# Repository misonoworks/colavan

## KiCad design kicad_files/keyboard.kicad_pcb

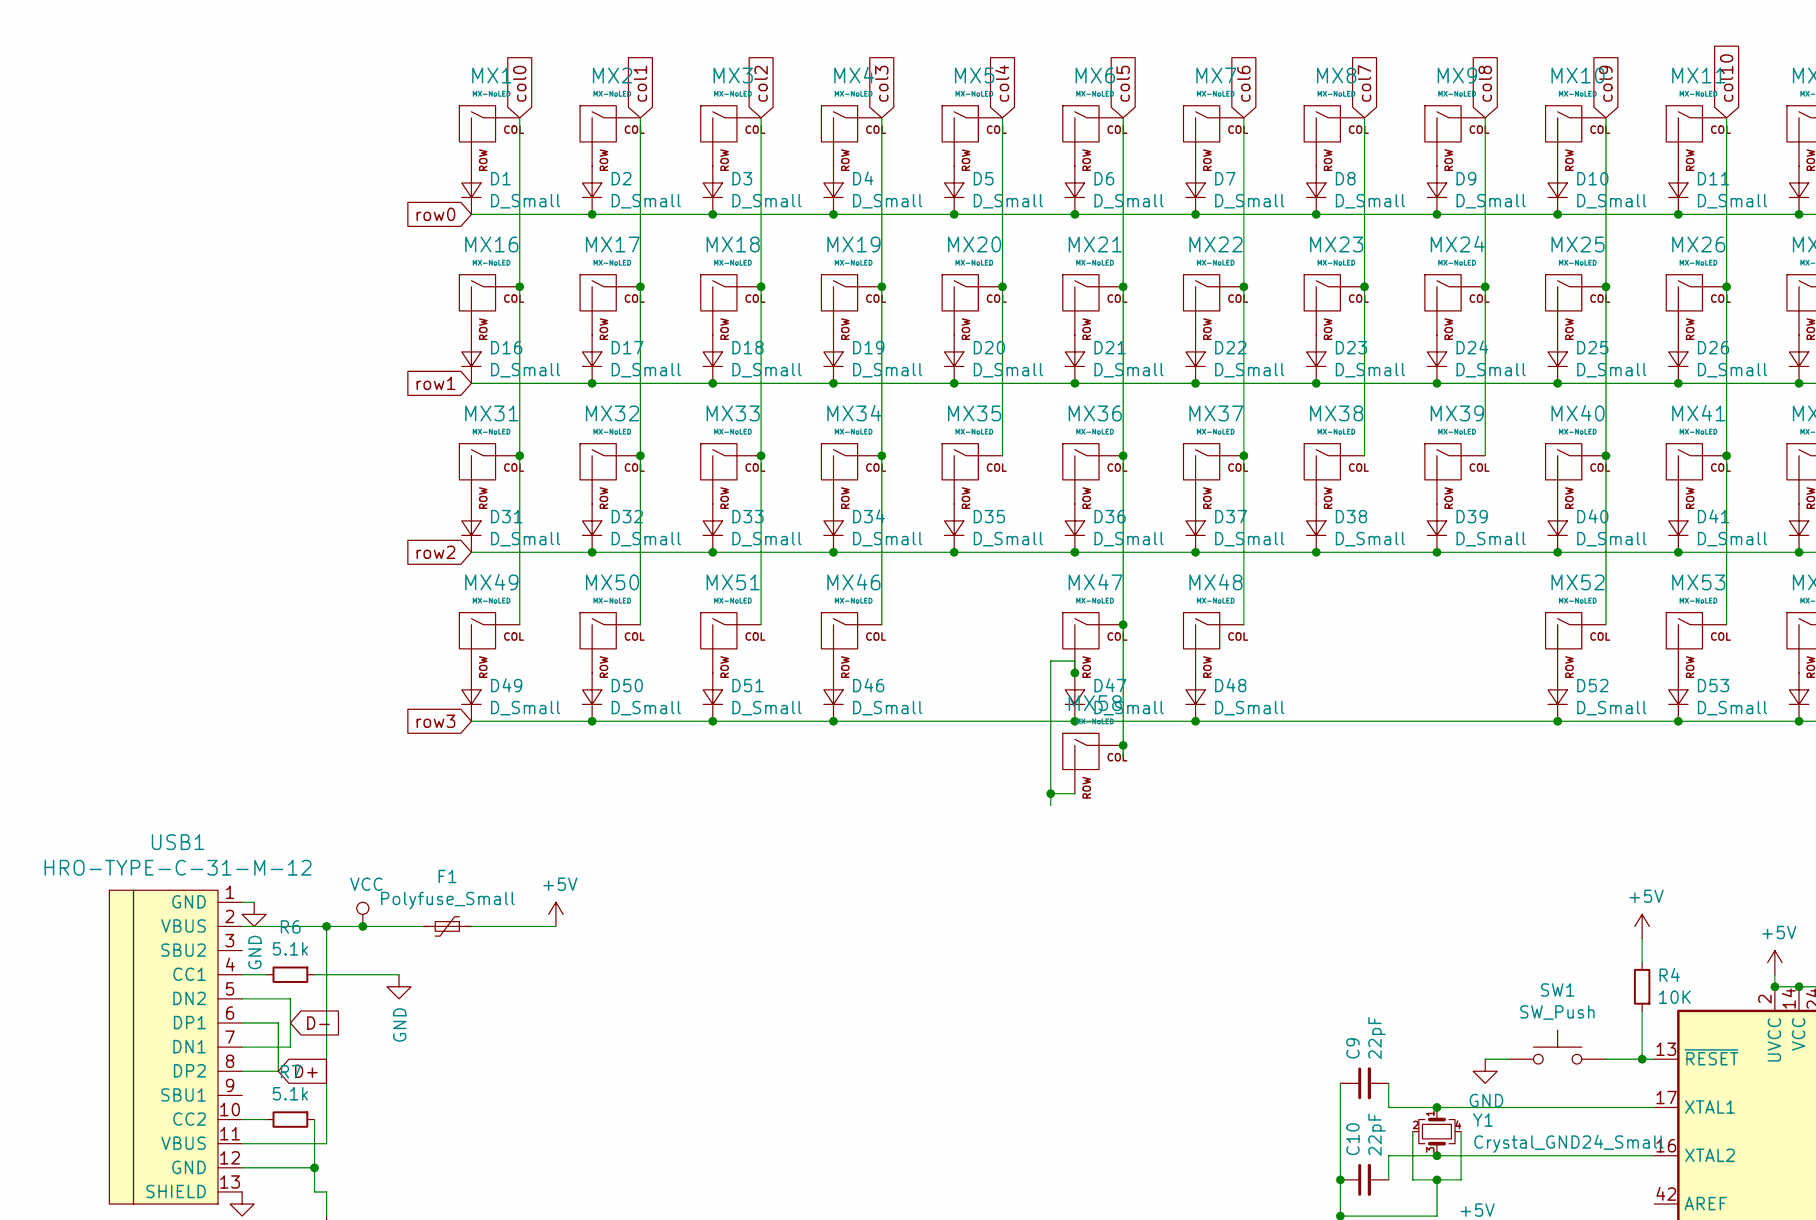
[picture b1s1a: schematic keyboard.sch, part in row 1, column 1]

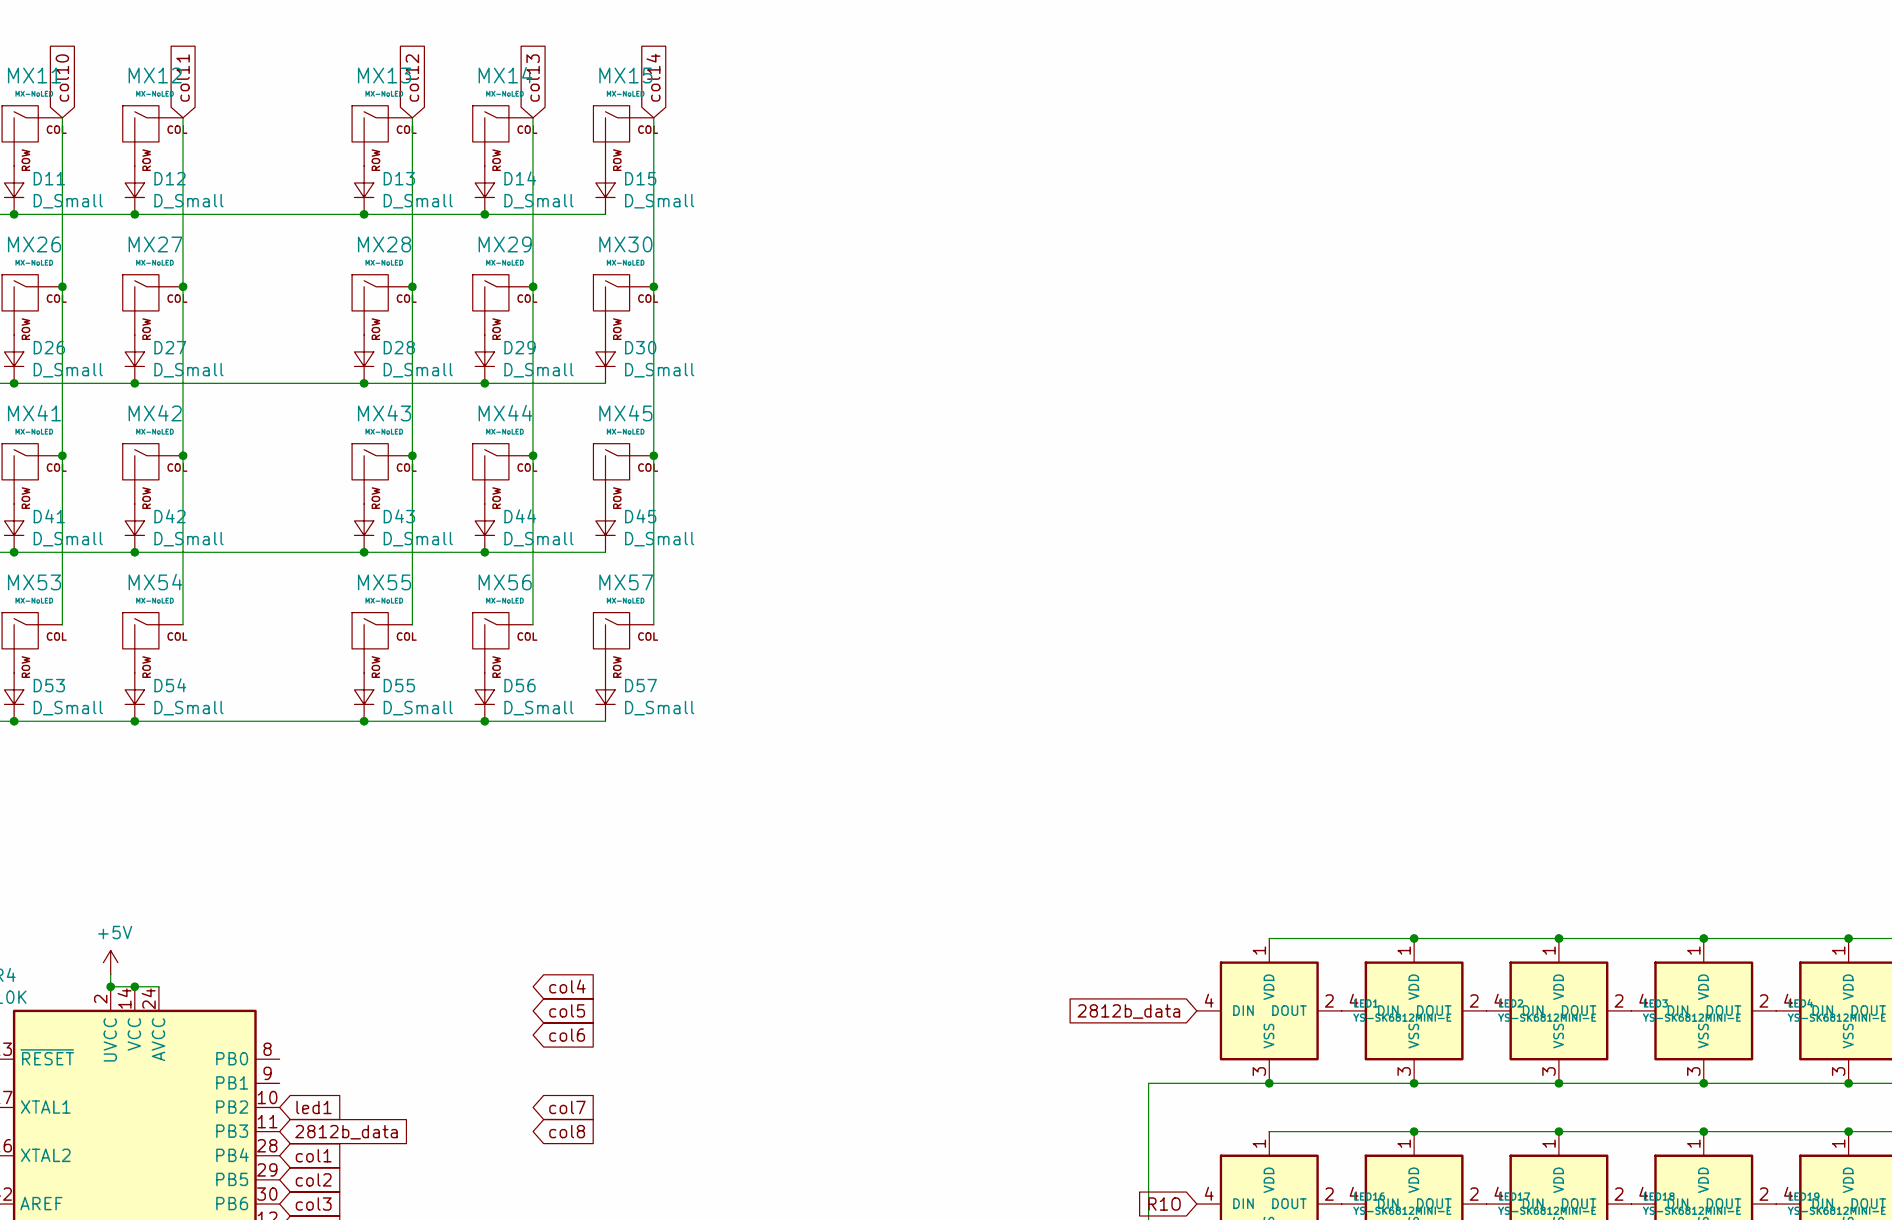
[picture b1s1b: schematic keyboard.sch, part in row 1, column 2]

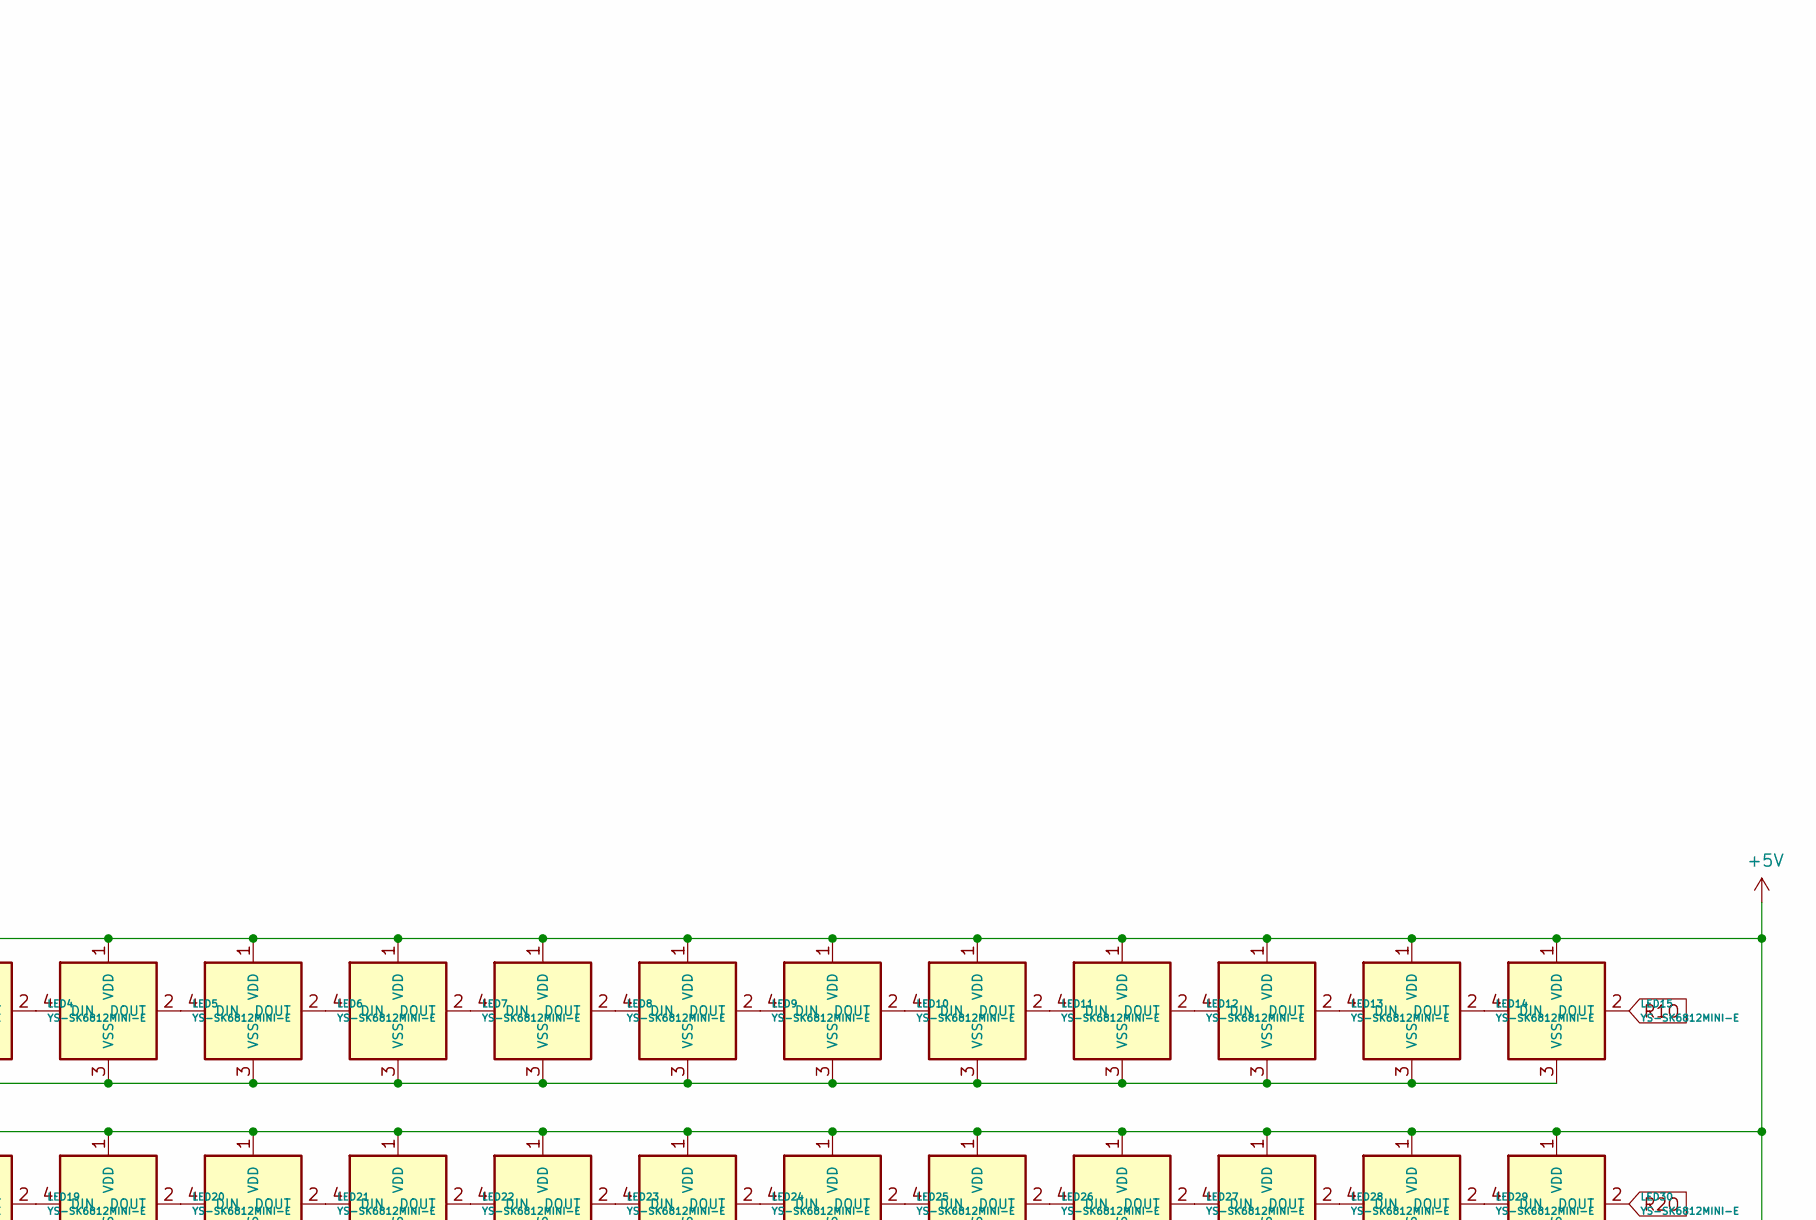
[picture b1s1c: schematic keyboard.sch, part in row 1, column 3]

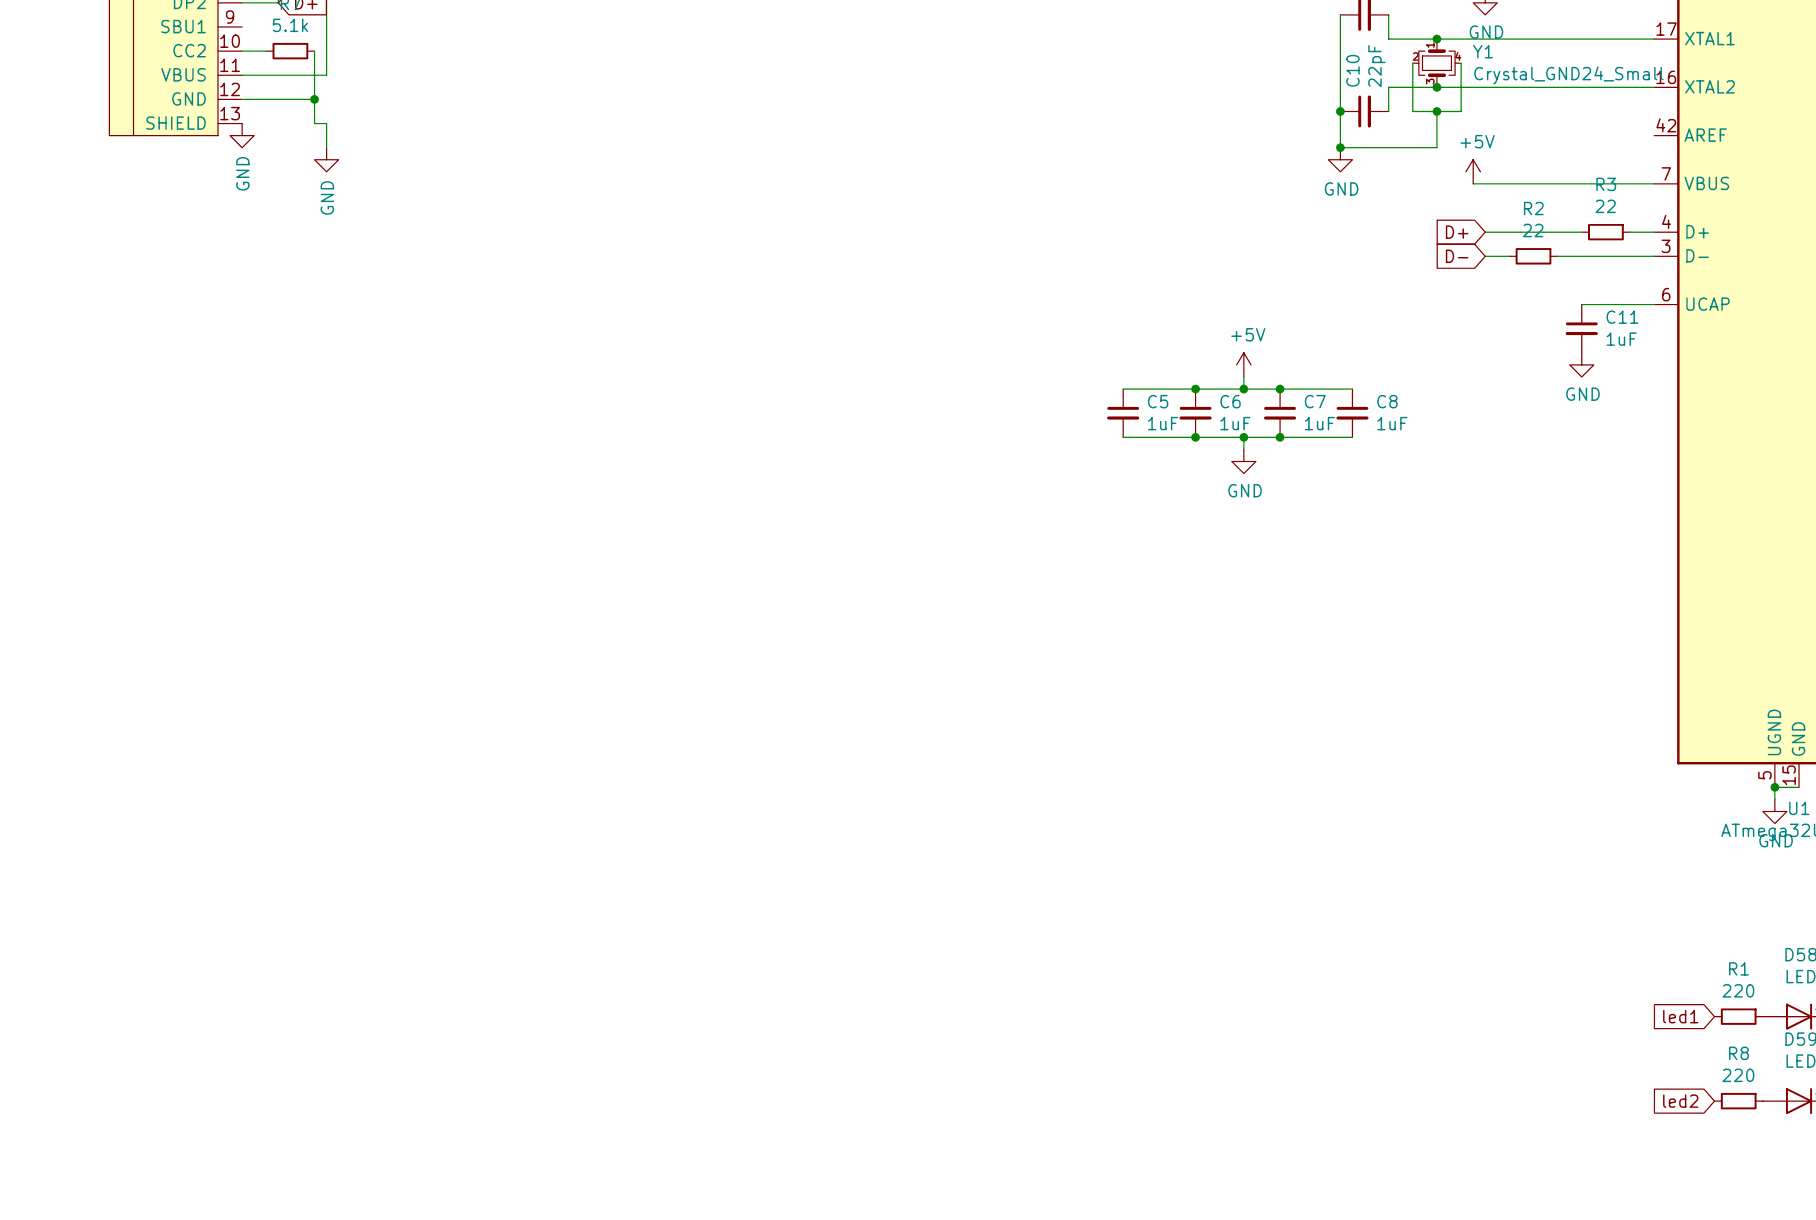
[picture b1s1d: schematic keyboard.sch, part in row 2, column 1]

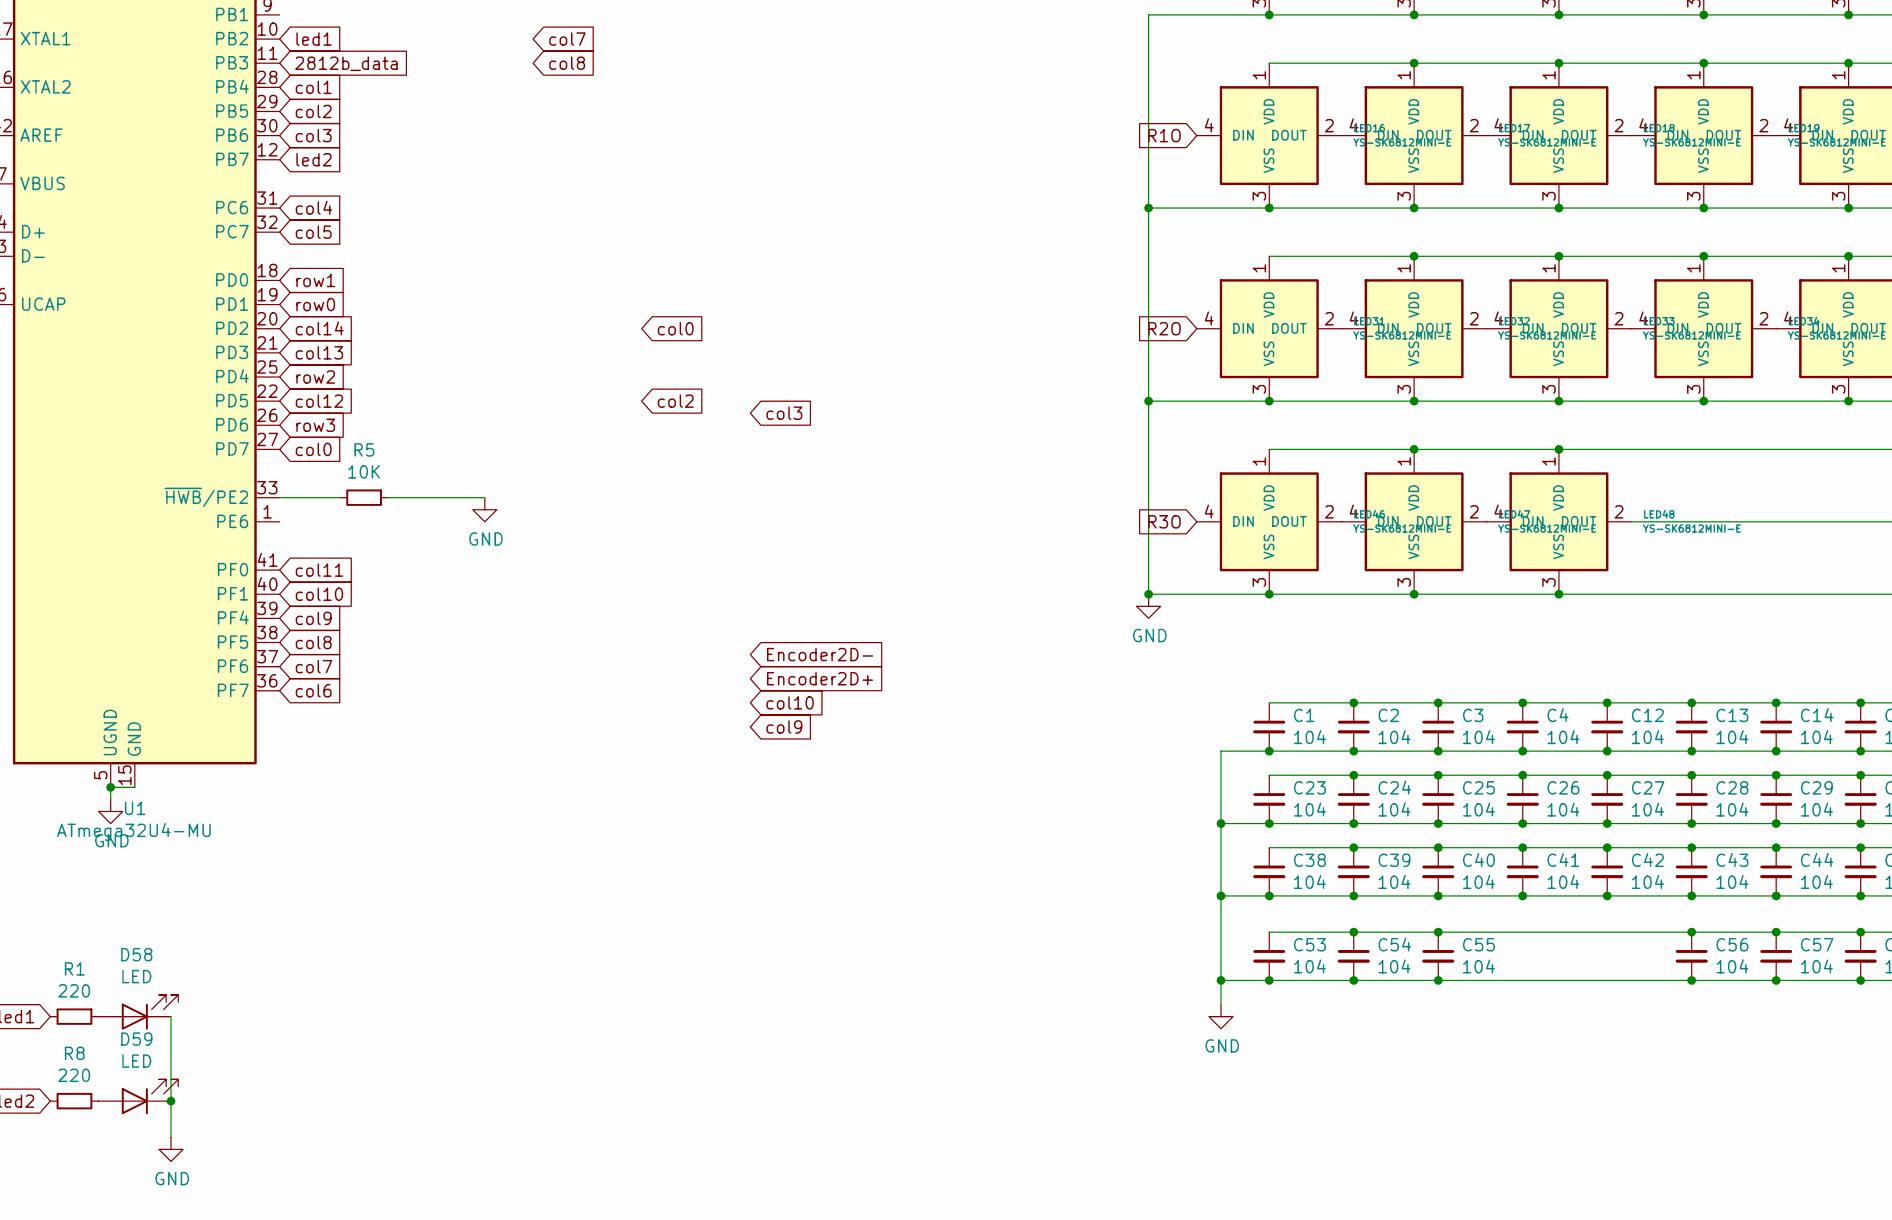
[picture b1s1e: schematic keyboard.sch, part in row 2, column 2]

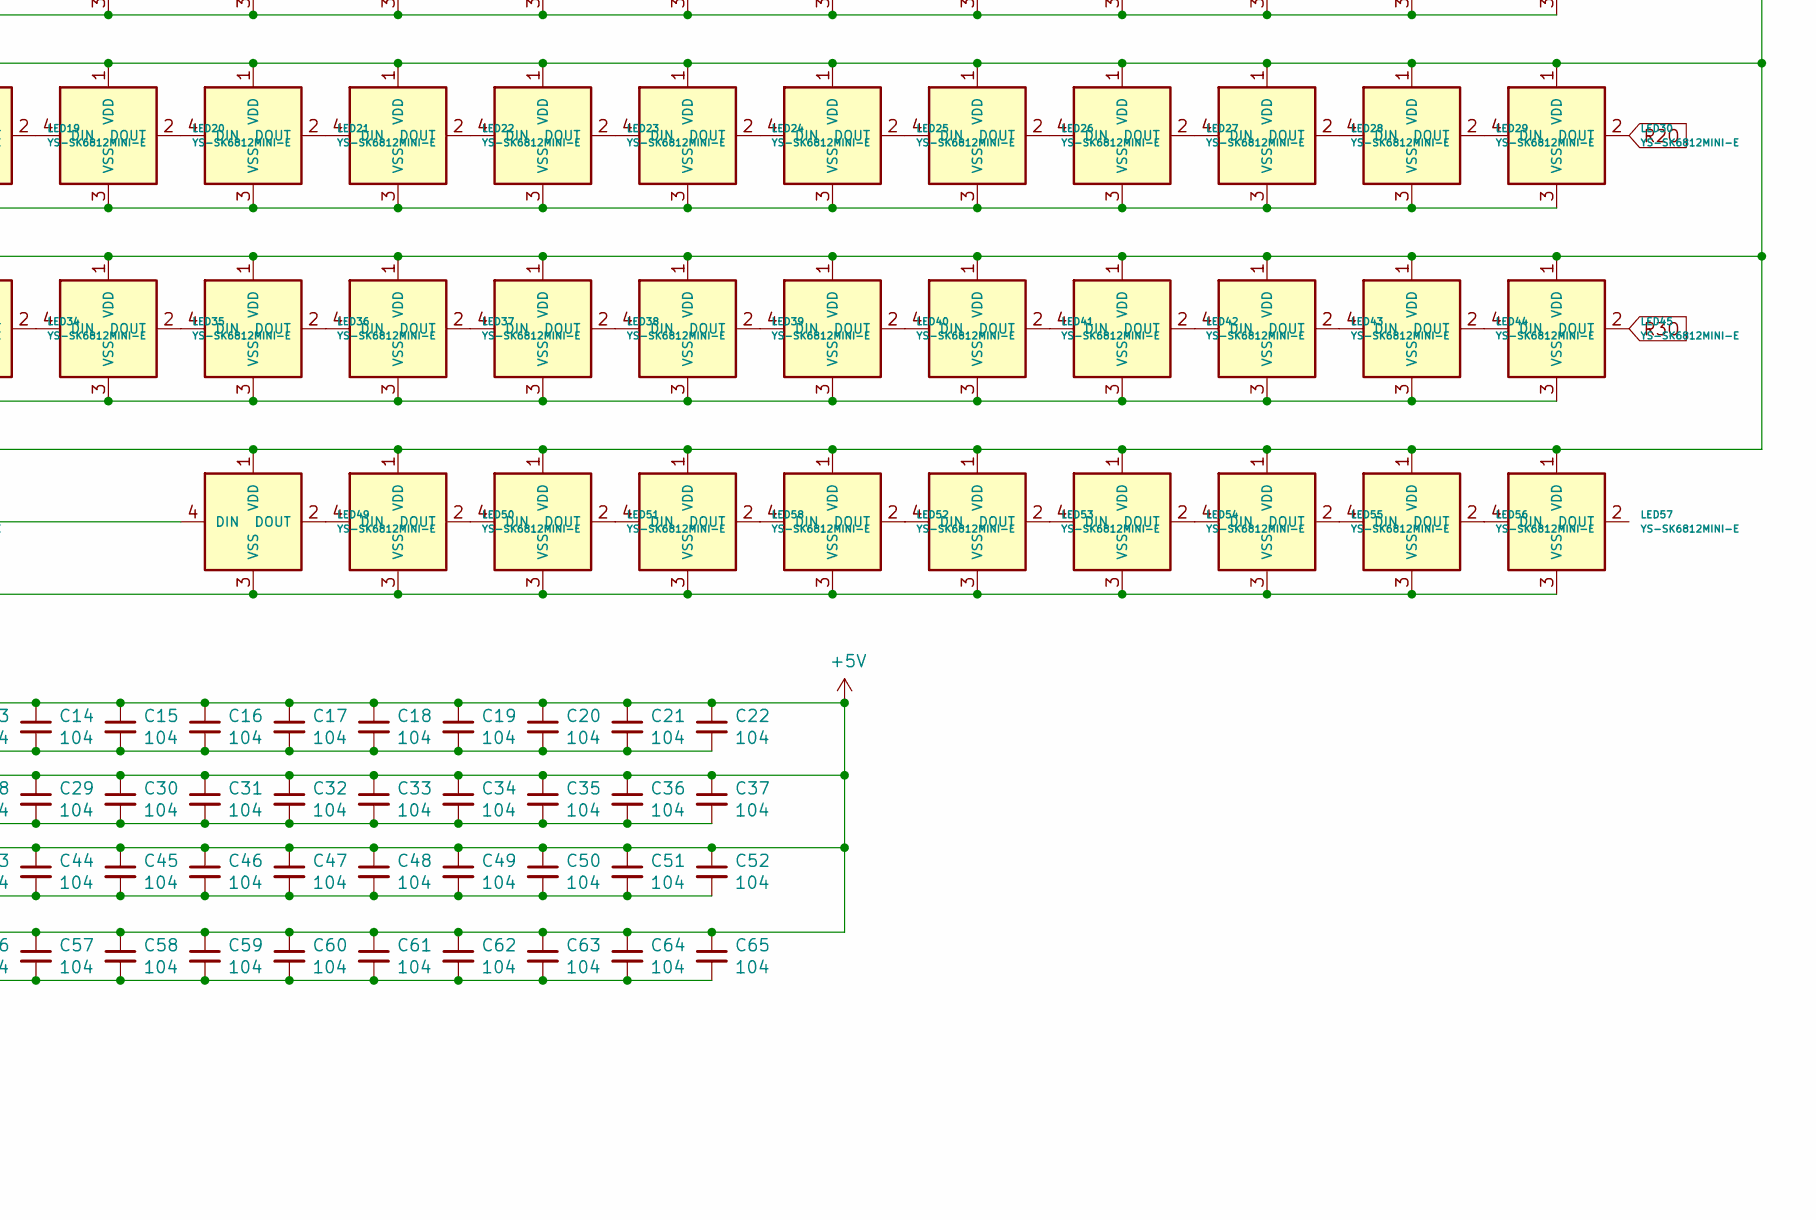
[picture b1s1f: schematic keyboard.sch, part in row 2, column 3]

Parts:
C1, C2, C3, C4, C12, C13, C14, C15, C16, C17, C18, C19, C20, C21, C22, C23, C24, C25, C26, C27, C28, C29, C30, C31, C32, C33, C34, C35, C36, C37, C38, C39, C40, C41, C42, C43, C44, C45, C46, C47, C48, C49, C50, C51, C52, C53, C54, C55, C56, C57, C58, C59, C60, C61, C62, C63, C64, C65: 104; C_0402_1005Metric
C5, C6, C7, C8, C11: 1uF; C_0402_1005Metric
C9, C10: 22pF; C_0402_1005Metric
D1, D2, D3, D4, D5, D6, D7, D8, D9, D10, D11, D12, D13, D14, D15, D16, D17, D18, D19, D20, D21, D22, D23, D24, D25, D26, D27, D28, D29, D30, D31, D32, D33, D34, D35, D36, D37, D38, D39, D40, D41, D42, D43, D44, D45, D46, D47, D48, D49, D50, D51, D52, D53, D54, D55, D56, D57: D_Small; D_SOD-123
D58, D59: LED; LED_D3.0mm
F1: Polyfuse_Small; Fuse_1206_3216Metric
LED1, LED2, LED3, LED4, LED5, LED6, LED7, LED8, LED9, LED10, LED11, LED12, LED13, LED14, LED15, LED16, LED17, LED18, LED19, LED20, LED21, LED22, LED23, LED24, LED25, LED26, LED27, LED28, LED29, LED30, LED31, LED32, LED33, LED34, LED35, LED36, LED37, LED38, LED39, LED40, LED41, LED42, LED43, LED44, LED45, LED46, LED47, LED48, LED49, LED50, LED51, LED52, LED53, LED54, LED55, LED56, LED57, LED58: YS-SK6812MINI-E
MX1, MX2, MX3, MX4, MX5, MX6, MX7, MX8, MX9, MX10, MX11, MX13, MX14, MX15, MX17, MX18, MX19, MX20, MX21, MX22, MX23, MX24, MX25, MX26, MX28, MX29, MX30, MX32, MX33, MX34, MX35, MX36, MX37, MX38, MX39, MX40, MX41, MX42, MX43, MX44, MX45, MX50, MX51, MX52, MX53, MX55, MX56, MX57: MX-NoLED; MX-1U-NoLED
MX12, MX31: MX-NoLED; MX-1.75U-NoLED
MX16, MX49, MX54, MX58: MX-NoLED; MX-1.25U-NoLED
MX27: MX-NoLED; MX-1.5U-NoLED
MX46: MX-NoLED; MX-2.25U-ReversedStabilizers-NoLED
MX47: MX-NoLED; MX-6.25U-ReversedStabilizers-NoLED
MX48: MX-NoLED; MX-2.75U-ReversedStabilizers-NoLED
R1, R8: 220; R_0402_1005Metric
R2, R3: 22; R_0603_1608Metric
R4, R5: 10K; R_0603_1608Metric
R6, R7: 5.1k; R_0603_1608Metric
SW1: SW_Push; SKQG-1155865
U1: ATmega32U4-MU; QFN-44-1EP_7x7mm_P0.5mm_EP5.2x5.2mm
USB1: HRO-TYPE-C-31-M-12; HRO-TYPE-C-31-M-12-HandSoldering
Y1: Crystal_GND24_Small; Crystal_SMD_3225-4Pin_3.2x2.5mm

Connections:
2812b_data: LED1.4 (DIN), U1.11 (PB3)
+5V: C1.1, C2.1, C3.1, C4.1, C5.1, C6.1, C7.1, C8.1, C12.1, C13.1, C14.1, C15.1, C16.1, C17.1, C18.1, C19.1, C20.1, C21.1, C22.1, C23.1, C24.1, C25.1, C26.1, C27.1, C28.1, C29.1, C30.1, C31.1, C32.1, C33.1, C34.1, C35.1, C36.1, C37.1, C38.1, C39.1, C40.1, C41.1, C42.1, C43.1, C44.1, C45.1, C46.1, C47.1, C48.1, C49.1, C50.1, C51.1, C52.1, C53.1, C54.1, C55.1, C56.1, C57.1, C58.1, C59.1, C60.1, C61.1, C62.1, C63.1, C64.1, C65.1, F1.1, LED1.1 (VDD), LED2.1 (VDD), LED3.1 (VDD), LED4.1 (VDD), LED5.1 (VDD), LED6.1 (VDD), LED7.1 (VDD), LED8.1 (VDD), LED9.1 (VDD), LED10.1 (VDD), LED11.1 (VDD), LED12.1 (VDD), LED13.1 (VDD), LED14.1 (VDD), LED15.1 (VDD), LED16.1 (VDD), LED17.1 (VDD), LED18.1 (VDD), LED19.1 (VDD), LED20.1 (VDD), LED21.1 (VDD), LED22.1 (VDD), LED23.1 (VDD), LED24.1 (VDD), LED25.1 (VDD), LED26.1 (VDD), LED27.1 (VDD), LED28.1 (VDD), LED29.1 (VDD), LED30.1 (VDD), LED31.1 (VDD), LED32.1 (VDD), LED33.1 (VDD), LED34.1 (VDD), LED35.1 (VDD), LED36.1 (VDD), LED37.1 (VDD), LED38.1 (VDD), LED39.1 (VDD), LED40.1 (VDD), LED41.1 (VDD), LED42.1 (VDD), LED43.1 (VDD), LED44.1 (VDD), LED45.1 (VDD), LED46.1 (VDD), LED47.1 (VDD), LED48.1 (VDD), LED49.1 (VDD), LED50.1 (VDD), LED51.1 (VDD), LED52.1 (VDD), LED53.1 (VDD), LED54.1 (VDD), LED55.1 (VDD), LED56.1 (VDD), LED57.1 (VDD), LED58.1 (VDD), R4.2, U1.2 (UVCC), U1.7 (VBUS), U1.14 (VCC), U1.24 (AVCC), U1.34 (VCC), U1.44 (AVCC)
D+: R3.2, USB1.6 (DP1), USB1.8 (DP2)
D-: R2.2, USB1.5 (DN2), USB1.7 (DN1)
GND: C1.2, C2.2, C3.2, C4.2, C5.2, C6.2, C7.2, C8.2, C9.1, C10.1, C11.2, C12.2, C13.2, C14.2, C15.2, C16.2, C17.2, C18.2, C19.2, C20.2, C21.2, C22.2, C23.2, C24.2, C25.2, C26.2, C27.2, C28.2, C29.2, C30.2, C31.2, C32.2, C33.2, C34.2, C35.2, C36.2, C37.2, C38.2, C39.2, C40.2, C41.2, C42.2, C43.2, C44.2, C45.2, C46.2, C47.2, C48.2, C49.2, C50.2, C51.2, C52.2, C53.2, C54.2, C55.2, C56.2, C57.2, C58.2, C59.2, C60.2, C61.2, C62.2, C63.2, C64.2, C65.2, D58.1 (K), D59.1 (K), LED1.3 (VSS), LED2.3 (VSS), LED3.3 (VSS), LED4.3 (VSS), LED5.3 (VSS), LED6.3 (VSS), LED7.3 (VSS), LED8.3 (VSS), LED9.3 (VSS), LED10.3 (VSS), LED11.3 (VSS), LED12.3 (VSS), LED13.3 (VSS), LED14.3 (VSS), LED15.3 (VSS), LED16.3 (VSS), LED17.3 (VSS), LED18.3 (VSS), LED19.3 (VSS), LED20.3 (VSS), LED21.3 (VSS), LED22.3 (VSS), LED23.3 (VSS), LED24.3 (VSS), LED25.3 (VSS), LED26.3 (VSS), LED27.3 (VSS), LED28.3 (VSS), LED29.3 (VSS), LED30.3 (VSS), LED31.3 (VSS), LED32.3 (VSS), LED33.3 (VSS), LED34.3 (VSS), LED35.3 (VSS), LED36.3 (VSS), LED37.3 (VSS), LED38.3 (VSS), LED39.3 (VSS), LED40.3 (VSS), LED41.3 (VSS), LED42.3 (VSS), LED43.3 (VSS), LED44.3 (VSS), LED45.3 (VSS), LED46.3 (VSS), LED47.3 (VSS), LED48.3 (VSS), LED49.3 (VSS), LED50.3 (VSS), LED51.3 (VSS), LED52.3 (VSS), LED53.3 (VSS), LED54.3 (VSS), LED55.3 (VSS), LED56.3 (VSS), LED57.3 (VSS), LED58.3 (VSS), R5.1, R6.1, R7.1, SW1.1, U1.5 (UGND), U1.15 (GND), U1.23 (GND), U1.35 (GND), U1.43 (GND), U1.45 (GND), USB1.1 (GND), USB1.12 (GND), USB1.13 (SHIELD), Y1.2, Y1.4
unnamed: C9.2, U1.17 (XTAL1), Y1.1
unnamed: C10.2, U1.16 (XTAL2), Y1.3
unnamed: C11.1, U1.6 (UCAP)
unnamed: D1.2 (A), MX1.2 (ROW)
unnamed: D2.2 (A), MX2.2 (ROW)
unnamed: D3.2 (A), MX3.2 (ROW)
unnamed: D4.2 (A), MX4.2 (ROW)
unnamed: D5.2 (A), MX5.2 (ROW)
unnamed: D6.2 (A), MX6.2 (ROW)
unnamed: D7.2 (A), MX7.2 (ROW)
unnamed: D8.2 (A), MX8.2 (ROW)
unnamed: D9.2 (A), MX9.2 (ROW)
unnamed: D10.2 (A), MX10.2 (ROW)
unnamed: D11.2 (A), MX11.2 (ROW)
unnamed: D12.2 (A), MX12.2 (ROW)
unnamed: D13.2 (A), MX13.2 (ROW)
unnamed: D14.2 (A), MX14.2 (ROW)
unnamed: D15.2 (A), MX15.2 (ROW)
unnamed: D16.2 (A), MX16.2 (ROW)
unnamed: D17.2 (A), MX17.2 (ROW)
unnamed: D18.2 (A), MX18.2 (ROW)
unnamed: D19.2 (A), MX19.2 (ROW)
unnamed: D20.2 (A), MX20.2 (ROW)
unnamed: D21.2 (A), MX21.2 (ROW)
unnamed: D22.2 (A), MX22.2 (ROW)
unnamed: D23.2 (A), MX23.2 (ROW)
unnamed: D24.2 (A), MX24.2 (ROW)
unnamed: D25.2 (A), MX25.2 (ROW)
unnamed: D26.2 (A), MX26.2 (ROW)
unnamed: D27.2 (A), MX27.2 (ROW)
unnamed: D28.2 (A), MX28.2 (ROW)
unnamed: D29.2 (A), MX29.2 (ROW)
unnamed: D30.2 (A), MX30.2 (ROW)
unnamed: D31.2 (A), MX31.2 (ROW)
unnamed: D32.2 (A), MX32.2 (ROW)
unnamed: D33.2 (A), MX33.2 (ROW)
unnamed: D34.2 (A), MX34.2 (ROW)
unnamed: D35.2 (A), MX35.2 (ROW)
unnamed: D36.2 (A), MX36.2 (ROW)
unnamed: D37.2 (A), MX37.2 (ROW)
unnamed: D38.2 (A), MX38.2 (ROW)
unnamed: D39.2 (A), MX39.2 (ROW)
unnamed: D40.2 (A), MX40.2 (ROW)
unnamed: D41.2 (A), MX41.2 (ROW)
unnamed: D42.2 (A), MX42.2 (ROW)
unnamed: D43.2 (A), MX43.2 (ROW)
unnamed: D44.2 (A), MX44.2 (ROW)
unnamed: D45.2 (A), MX45.2 (ROW)
unnamed: D46.2 (A), MX46.2 (ROW)
unnamed: D47.2 (A), MX47.2 (ROW), MX58.2 (ROW)
unnamed: D48.2 (A), MX48.2 (ROW)
unnamed: D49.2 (A), MX49.2 (ROW)
unnamed: D50.2 (A), MX50.2 (ROW)
unnamed: D51.2 (A), MX51.2 (ROW)
unnamed: D52.2 (A), MX52.2 (ROW)
unnamed: D53.2 (A), MX53.2 (ROW)
unnamed: D54.2 (A), MX54.2 (ROW)
unnamed: D55.2 (A), MX55.2 (ROW)
unnamed: D56.2 (A), MX56.2 (ROW)
unnamed: D57.2 (A), MX57.2 (ROW)
unnamed: D58.2 (A), R1.1
unnamed: D59.2 (A), R8.1
unnamed: LED1.2 (DOUT), LED2.4 (DIN)
unnamed: LED2.2 (DOUT), LED3.4 (DIN)
unnamed: LED3.2 (DOUT), LED4.4 (DIN)
unnamed: LED4.2 (DOUT), LED5.4 (DIN)
unnamed: LED5.2 (DOUT), LED6.4 (DIN)
unnamed: LED6.2 (DOUT), LED7.4 (DIN)
unnamed: LED7.2 (DOUT), LED8.4 (DIN)
unnamed: LED8.2 (DOUT), LED9.4 (DIN)
unnamed: LED10.2 (DOUT), LED11.4 (DIN)
unnamed: LED9.2 (DOUT), LED10.4 (DIN)
unnamed: LED11.2 (DOUT), LED12.4 (DIN)
unnamed: LED12.2 (DOUT), LED13.4 (DIN)
unnamed: LED13.2 (DOUT), LED14.4 (DIN)
unnamed: LED14.2 (DOUT), LED15.4 (DIN)
unnamed: LED16.2 (DOUT), LED17.4 (DIN)
unnamed: LED17.2 (DOUT), LED18.4 (DIN)
unnamed: LED18.2 (DOUT), LED19.4 (DIN)
unnamed: LED19.2 (DOUT), LED20.4 (DIN)
unnamed: LED20.2 (DOUT), LED21.4 (DIN)
unnamed: LED21.2 (DOUT), LED22.4 (DIN)
unnamed: LED22.2 (DOUT), LED23.4 (DIN)
unnamed: LED23.2 (DOUT), LED24.4 (DIN)
unnamed: LED24.2 (DOUT), LED25.4 (DIN)
unnamed: LED25.2 (DOUT), LED26.4 (DIN)
unnamed: LED26.2 (DOUT), LED27.4 (DIN)
unnamed: LED27.2 (DOUT), LED28.4 (DIN)
unnamed: LED28.2 (DOUT), LED29.4 (DIN)
unnamed: LED29.2 (DOUT), LED30.4 (DIN)
unnamed: LED31.2 (DOUT), LED32.4 (DIN)
unnamed: LED32.2 (DOUT), LED33.4 (DIN)
unnamed: LED33.2 (DOUT), LED34.4 (DIN)
unnamed: LED34.2 (DOUT), LED35.4 (DIN)
unnamed: LED35.2 (DOUT), LED36.4 (DIN)
unnamed: LED36.2 (DOUT), LED37.4 (DIN)
unnamed: LED37.2 (DOUT), LED38.4 (DIN)
unnamed: LED38.2 (DOUT), LED39.4 (DIN)
unnamed: LED39.2 (DOUT), LED40.4 (DIN)
unnamed: LED40.2 (DOUT), LED41.4 (DIN)
unnamed: LED41.2 (DOUT), LED42.4 (DIN)
unnamed: LED42.2 (DOUT), LED43.4 (DIN)
unnamed: LED43.2 (DOUT), LED44.4 (DIN)
unnamed: LED44.2 (DOUT), LED45.4 (DIN)
unnamed: LED46.2 (DOUT), LED47.4 (DIN)
unnamed: LED47.2 (DOUT), LED48.4 (DIN)
unnamed: LED48.2 (DOUT), LED49.4 (DIN)
unnamed: LED49.2 (DOUT), LED50.4 (DIN)
unnamed: LED50.2 (DOUT), LED51.4 (DIN)
unnamed: LED51.2 (DOUT), LED58.4 (DIN)
unnamed: LED52.2 (DOUT), LED53.4 (DIN)
unnamed: LED52.4 (DIN), LED58.2 (DOUT)
unnamed: LED53.2 (DOUT), LED54.4 (DIN)
unnamed: LED54.2 (DOUT), LED55.4 (DIN)
unnamed: LED55.2 (DOUT), LED56.4 (DIN)
unnamed: LED56.2 (DOUT), LED57.4 (DIN)
unnamed: R2.1, U1.3 (D-)
unnamed: R3.1, U1.4 (D+)
unnamed: R4.1, SW1.2, U1.13 (~RESET)
unnamed: R5.2, U1.33 (~HWB~/PE2)
unnamed: R6.2, USB1.4 (CC1)
unnamed: R7.2, USB1.10 (CC2)
R1O: LED15.2 (DOUT), LED16.4 (DIN)
R2O: LED30.2 (DOUT), LED31.4 (DIN)
R3O: LED45.2 (DOUT), LED46.4 (DIN)
VCC: F1.2, USB1.2 (VBUS), USB1.11 (VBUS)
col0: MX1.1 (COL), MX16.1 (COL), MX31.1 (COL), MX49.1 (COL), U1.27 (PD7)
col1: MX2.1 (COL), MX17.1 (COL), MX32.1 (COL), MX50.1 (COL), U1.28 (PB4)
col2: MX3.1 (COL), MX18.1 (COL), MX33.1 (COL), MX51.1 (COL), U1.29 (PB5)
col3: MX4.1 (COL), MX19.1 (COL), MX34.1 (COL), MX46.1 (COL), U1.30 (PB6)
col4: MX5.1 (COL), MX20.1 (COL), MX35.1 (COL), U1.31 (PC6)
col5: MX6.1 (COL), MX21.1 (COL), MX36.1 (COL), MX47.1 (COL), MX58.1 (COL), U1.32 (PC7)
col6: MX7.1 (COL), MX22.1 (COL), MX37.1 (COL), MX48.1 (COL), U1.36 (PF7)
col7: MX8.1 (COL), MX23.1 (COL), MX38.1 (COL), U1.37 (PF6)
col8: MX9.1 (COL), MX24.1 (COL), MX39.1 (COL), U1.38 (PF5)
col9: MX10.1 (COL), MX25.1 (COL), MX40.1 (COL), MX52.1 (COL), U1.39 (PF4)
col10: MX11.1 (COL), MX26.1 (COL), MX41.1 (COL), MX53.1 (COL), U1.40 (PF1)
col11: MX12.1 (COL), MX27.1 (COL), MX42.1 (COL), MX54.1 (COL), U1.41 (PF0)
col12: MX13.1 (COL), MX28.1 (COL), MX43.1 (COL), MX55.1 (COL), U1.22 (PD5)
col13: MX14.1 (COL), MX29.1 (COL), MX44.1 (COL), MX56.1 (COL), U1.21 (PD3)
col14: MX15.1 (COL), MX30.1 (COL), MX45.1 (COL), MX57.1 (COL), U1.20 (PD2)
led1: R1.2, U1.10 (PB2)
led2: R8.2, U1.12 (PB7)
row0: D1.1 (K), D2.1 (K), D3.1 (K), D4.1 (K), D5.1 (K), D6.1 (K), D7.1 (K), D8.1 (K), D9.1 (K), D10.1 (K), D11.1 (K), D12.1 (K), D13.1 (K), D14.1 (K), D15.1 (K), U1.19 (PD1)
row1: D16.1 (K), D17.1 (K), D18.1 (K), D19.1 (K), D20.1 (K), D21.1 (K), D22.1 (K), D23.1 (K), D24.1 (K), D25.1 (K), D26.1 (K), D27.1 (K), D28.1 (K), D29.1 (K), D30.1 (K), U1.18 (PD0)
row2: D31.1 (K), D32.1 (K), D33.1 (K), D34.1 (K), D35.1 (K), D36.1 (K), D37.1 (K), D38.1 (K), D39.1 (K), D40.1 (K), D41.1 (K), D42.1 (K), D43.1 (K), D44.1 (K), D45.1 (K), U1.25 (PD4)
row3: D46.1 (K), D47.1 (K), D48.1 (K), D49.1 (K), D50.1 (K), D51.1 (K), D52.1 (K), D53.1 (K), D54.1 (K), D55.1 (K), D56.1 (K), D57.1 (K), U1.26 (PD6)

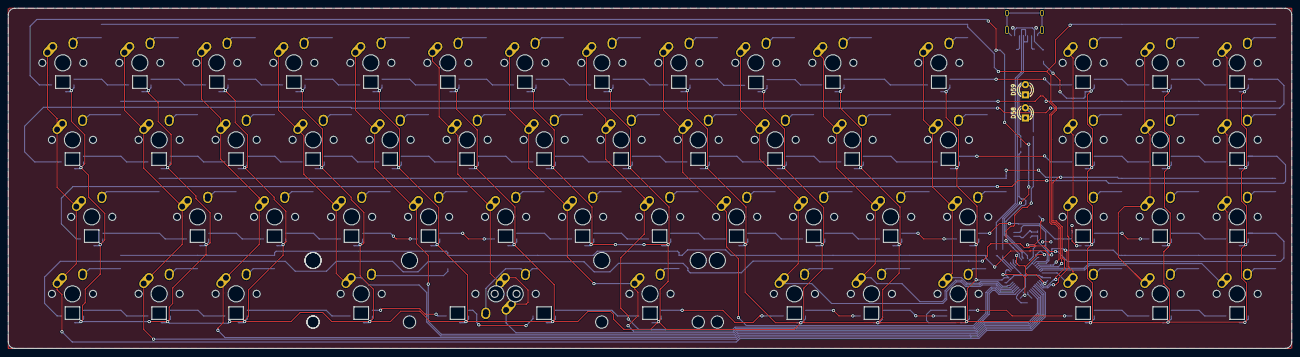
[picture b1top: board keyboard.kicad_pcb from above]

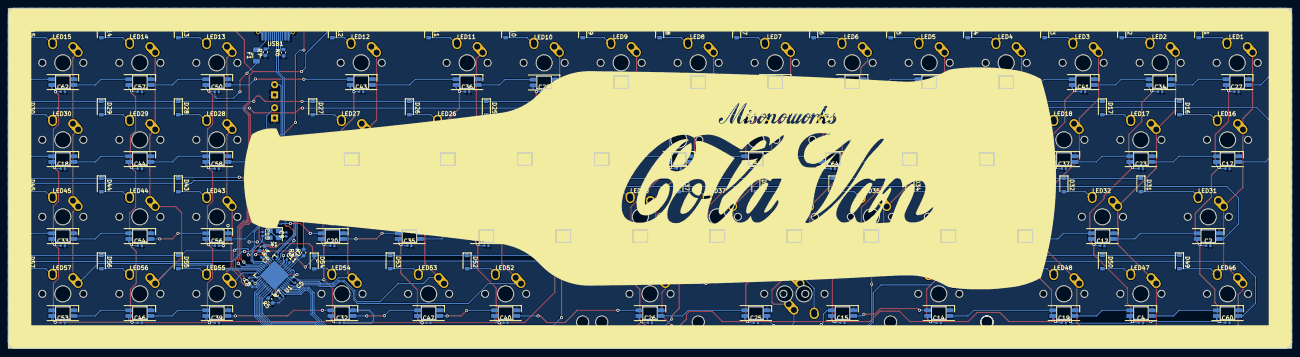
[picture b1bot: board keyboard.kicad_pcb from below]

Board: 2 copper layers, 317.5 x 84.1 mm, 253 parts (193 on the bottom side), 152 nets.

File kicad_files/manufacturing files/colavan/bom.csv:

Comment,Designator,Footprint,LCSC
"104","C1,C2,C3,C4,C12,C13,C14,C15,C16,C17,C18,C19,C20,C21,C22,C23,C24,C25,C26,C27,C28,C29,C30,C31,C32,C33,C34,C35,C36,C37,C38,C39,C40,C41,C42,C43,C44,C45,C46,C47,C48,C49,C50,C51,C52,C53,C54,C55,C56,C57,C58,C59,C60,C61,C62,C63,C64,C65","Capacitor_SMD:C_0402_1005Metric",""
"1uF","C11,C5,C6,C7,C8","Capacitor_SMD:C_0402_1005Metric",""
"22pF","C9,C10","Capacitor_SMD:C_0402_1005Metric",""
"D_Small","D1,D2,D3,D4,D5,D6,D7,D8,D9,D10,D11,D12,D16,D17,D18,D19,D20,D21,D22,D23,D24,D25,D26,D27,D31,D32,D33,D34,D35,D36,D37,D38,D39,D40,D41,D42,D49,D50,D51,D52,D53,D54,D46,D47,D48,D13,D14,D15,D28,D29,D30,D43,D44,D45,D55,D56,D57","Diode_SMD:D_SOD-123",""
"LED","D58,D59","LED_THT:LED_D3.0mm",""
"Polyfuse_Small","F1","Fuse:Fuse_1206_3216Metric",""
"YS-SK6812MINI-E","LED1,LED2,LED3,LED4,LED5,LED6,LED7,LED8,LED9,LED10,LED11,LED12,LED13,LED14,LED15,LED16,LED17,LED18,LED19,LED20,LED21,LED22,LED23,LED24,LED25,LED26,LED27,LED28,LED29,LED30,LED31,LED32,LED33,LED34,LED35,LED36,LED37,LED38,LED39,LED40,LED41,LED42,LED43,LED44,LED45,LED46,LED47,LED48,LED49,LED50,LED51,LED52,LED53,LED54,LED55,LED56,LED57,LED58","kbd:YS-SK6812MINI-E",""
"MX-NoLED","MX1,MX2,MX3,MX4,MX5,MX6,MX7,MX8,MX9,MX10,MX11,MX17,MX18,MX19,MX20,MX21,MX22,MX23,MX24,MX25,MX26,MX32,MX33,MX34,MX35,MX36,MX37,MX38,MX39,MX40,MX41,MX42,MX50,MX51,MX52,MX53,MX13,MX14,MX15,MX28,MX29,MX30,MX43,MX44,MX45,MX55,MX56,MX57","MX_Alps_Hybrid:MX-1U-NoLED",""
"MX-NoLED","MX12,MX31","MX_Alps_Hybrid:MX-1.75U-NoLED",""
"MX-NoLED","MX16,MX49,MX54,MX58","MX_Alps_Hybrid:MX-1.25U-NoLED",""
"MX-NoLED","MX27","MX_Alps_Hybrid:MX-1.5U-NoLED",""
"MX-NoLED","MX46","MX_Alps_Hybrid:MX-2.25U-ReversedStabilizers-NoLED",""
"MX-NoLED","MX47","MX_Alps_Hybrid:MX-6.25U-ReversedStabilizers-NoLED",""
"MX-NoLED","MX48","MX_Alps_Hybrid:MX-2.75U-ReversedStabilizers-NoLED",""
"22","R3,R2","Resistor_SMD:R_0603_1608Metric",""
"10K","R5,R4","Resistor_SMD:R_0603_1608Metric",""
"5.1k","R6,R7","Resistor_SMD:R_0603_1608Metric",""
"220","R8,R1","Resistor_SMD:R_0402_1005Metric",""
"SW_Push","SW1","random-keyboard-parts:SKQG-1155865",""
"ATmega32U4-MU","U1","Package_DFN_QFN:QFN-44-1EP_7x7mm_P0.5mm_EP5.2x5.2mm",""
"HRO-TYPE-C-31-M-12","USB1","Type-C:HRO-TYPE-C-31-M-12-HandSoldering",""
"Crystal_GND24_Small","Y1","Crystal:Crystal_SMD_3225-4Pin_3.2x2.5mm",""
